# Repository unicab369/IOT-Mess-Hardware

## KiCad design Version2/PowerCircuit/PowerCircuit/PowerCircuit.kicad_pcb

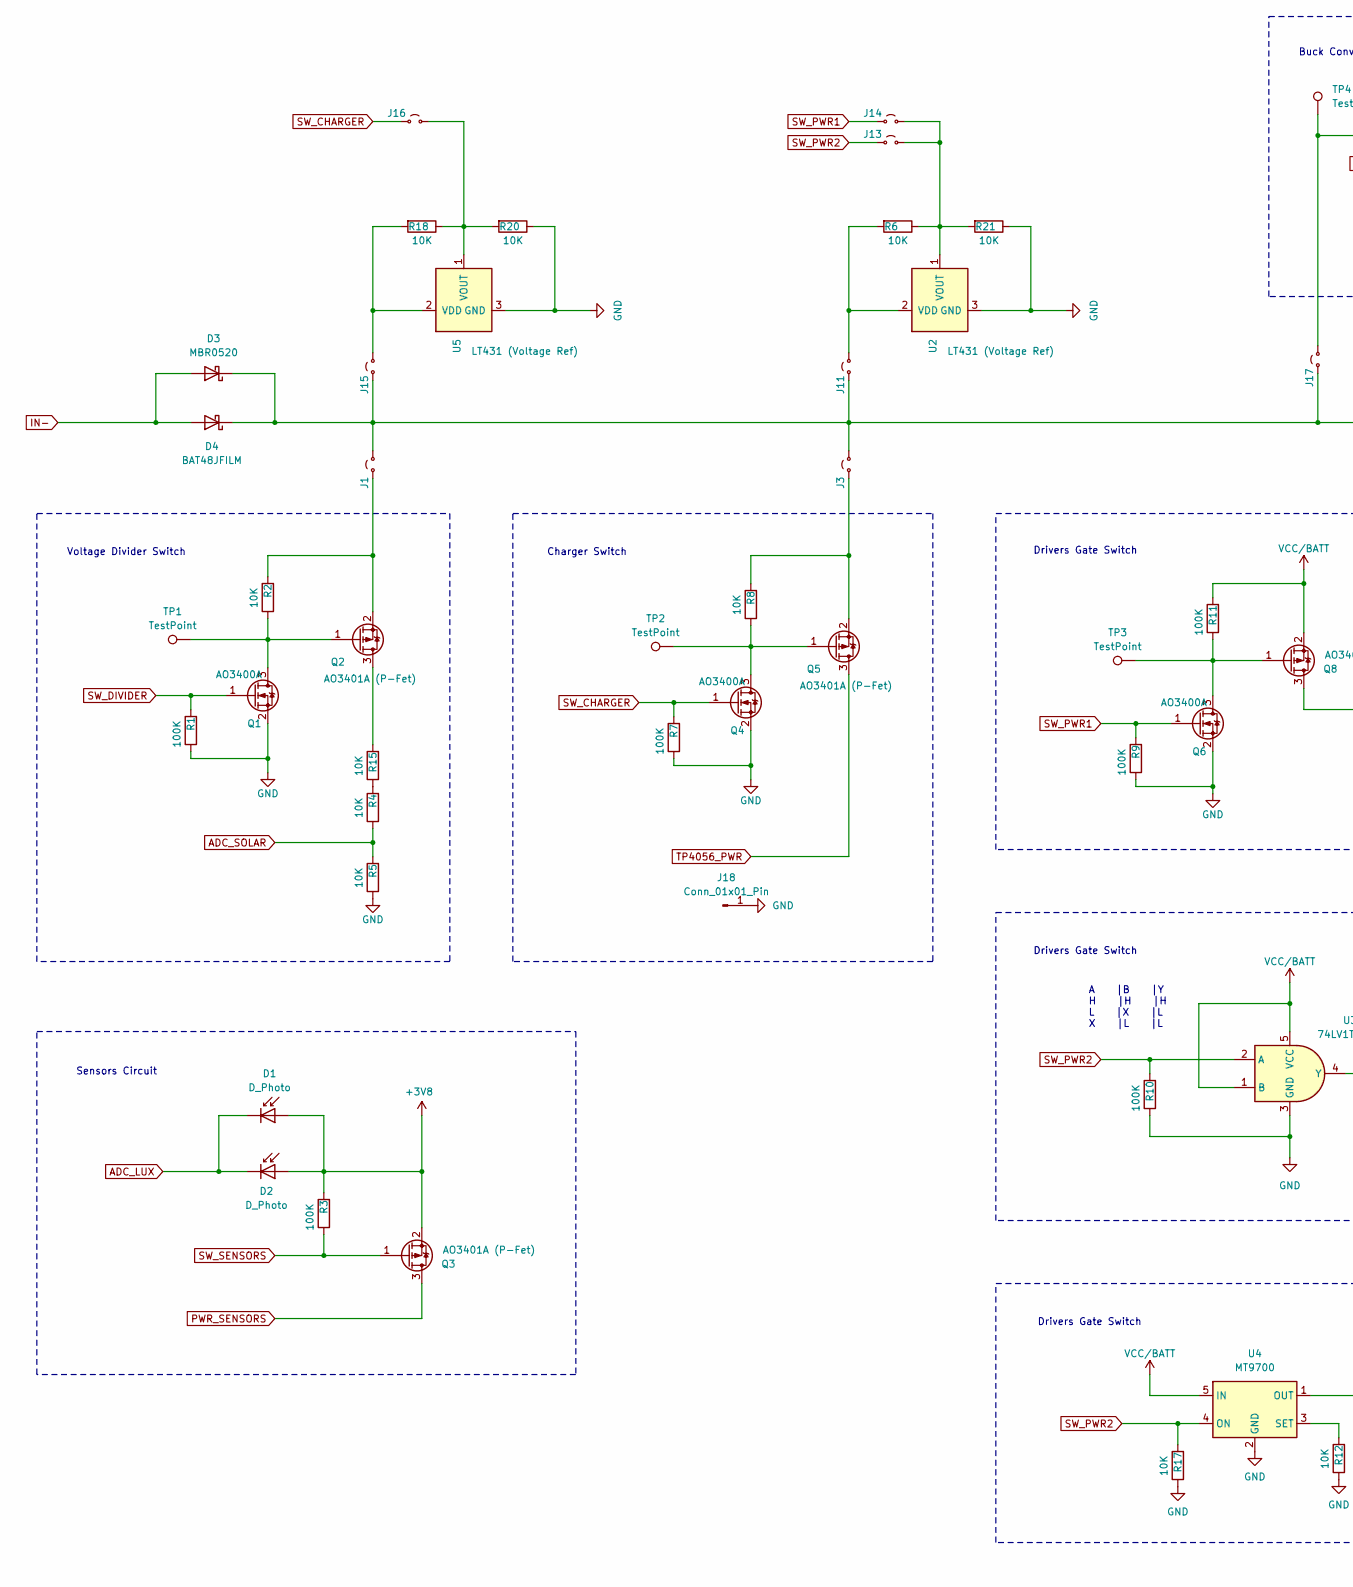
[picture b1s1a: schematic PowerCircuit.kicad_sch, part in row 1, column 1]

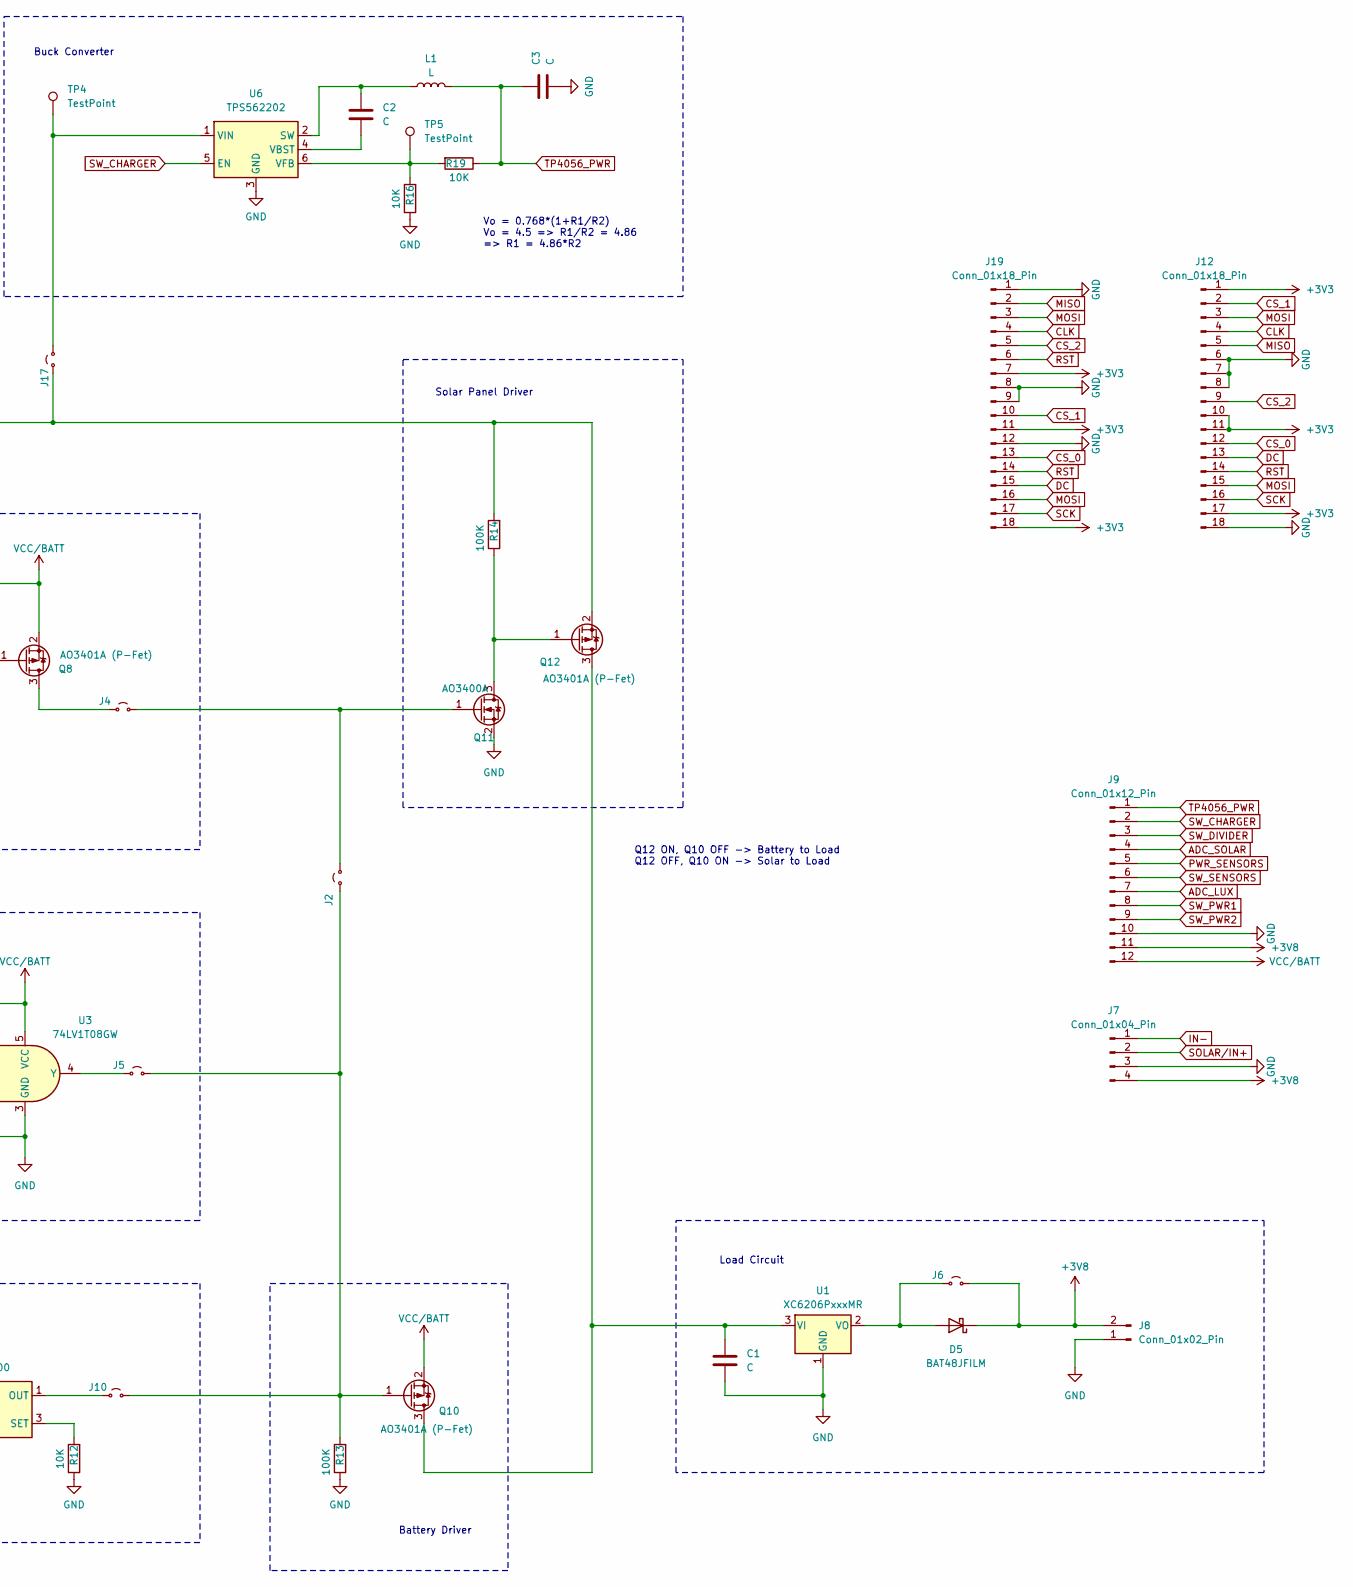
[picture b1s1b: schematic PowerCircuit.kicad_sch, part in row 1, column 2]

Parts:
C1, C2, C3: C; C_0603_1608Metric
D1: D_Photo; LED_0603_1608Metric
D2: D_Photo; LED_0805_2012Metric
D3: MBR0520; D_SOD-123
D4, D5: BAT48JFILM; D_SOD-323
J1, J2, J3, J4, J5, J6, J10, J11, J13, J14, J15, J16, J17: Jumper_2; Jumpper-triangle
J7: Conn_01x04_Pin; PinHeader_1x04_P2.54mm_Vertical
J8: Conn_01x02_Pin; PinHeader_1x02_P1.00mm_Vertical
J9: Conn_01x12_Pin; PinHeader_1x12_P2.54mm_Vertical
J12, J19: Conn_01x18_Pin; PinHeader_1x18_P2.54mm_Vertical
J18: Conn_01x01_Pin; PinHeader_1x01_P2.54mm_Vertical
L1: L; L_Neosid_SMS-ME3010
Q1, Q4, Q6, Q11: AO3400A; SOT-23
Q2, Q3, Q5, Q8, Q10, Q12: AO3401A (P-Fet); SOT-23
R1, R3, R7, R9, R10, R11, R13, R14: 100K; R_0805_2012Metric
R2, R4, R5, R6, R8, R12, R15, R16, R17, R18, R19, R20, R21: 10K; R_0805_2012Metric
TP1, TP2, TP3, TP4, TP5: TestPoint; PinHeader_1x01_P1.00mm_Vertical
U1: XC6206PxxxMR; SOT-23-3
U2, U5: LT431 (Voltage Ref); SOT-23
U3: 74LV1T08GW; SOT-353_SC-70-5
U4: MT9700; SOT-23-5
U6: TPS562202; SOT-563

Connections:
+3V3: J12.1, J12.10, J12.11, J12.17, J19.7, J19.11, J19.18
+3V8: D1.2 (A), D2.2 (A), D5.1 (K), J6.2 (B), J7.4, J8.2, J9.11, Q3.2 (S), R3.2
ADC_LUX: D1.1 (K), D2.1 (K), J9.7
ADC_SOLAR: J9.4, R4.1, R5.2
CLK: J12.4, J19.4
CS_0: J12.12, J19.13
CS_1: J12.2, J19.10
CS_2: J12.9, J19.5
DC: J12.13, J19.15
GND: C1.2, C3.1, J7.3, J8.1, J9.10, J12.6, J12.7, J12.8, J12.18, J18.1, J19.1, J19.8, J19.9, J19.12, Q1.2 (S), Q4.2 (S), Q6.2 (S), Q11.2 (S), R1.1, R5.1, R7.1, R9.1, R10.1, R12.1, R13.1, R16.1, R17.1, R20.1, R21.1, U1.1 (GND), U2.3 (GND), U3.3 (GND), U4.2 (GND), U5.3 (GND), U6.3 (GND)
IN-: D3.2 (A), D4.2 (A), J7.1
MISO: J12.5, J19.2
MOSI: J12.3, J12.15, J19.3, J19.16
unnamed: D3.1 (K), D4.1 (K), J1.2 (B), J3.2 (B), J11.1 (A), J15.1 (A), J17.1 (A), Q12.2 (S), R14.2
unnamed: D5.2 (A), J6.1 (A), U1.2 (VO)
unnamed: J1.1 (A), Q2.2 (S), R2.2
unnamed: J2.2 (B), J4.2 (B), Q11.1 (G)
unnamed: J3.1 (A), Q5.2 (S), R8.2
unnamed: J4.1 (A), Q8.3 (D)
unnamed: J5.1 (A), U3.4 (Y)
unnamed: J10.1 (A), U4.1 (OUT)
unnamed: J2.1 (A), J5.2 (B), J10.2 (B), Q10.1 (G), R13.2
unnamed: J11.2 (B), R6.2, U2.2 (VDD)
unnamed: J13.2 (B), J14.2 (B), R6.1, R21.2, U2.1 (VOUT)
unnamed: J15.2 (B), R18.2, U5.2 (VDD)
unnamed: J16.2 (B), R18.1, R20.2, U5.1 (VOUT)
unnamed: J17.2 (B), TP4.1, U6.1 (VIN)
unnamed: Q1.3 (D), Q2.1 (G), R2.1, TP1.1
unnamed: Q2.3 (D), R15.2
unnamed: Q4.3 (D), Q5.1 (G), R8.1, TP2.1
unnamed: Q6.3 (D), Q8.1 (G), R11.1, TP3.1
unnamed: C1.1, Q10.3 (D), Q12.3 (D), U1.3 (VI)
unnamed: Q11.3 (D), Q12.1 (G), R14.1
unnamed: R4.2, R15.1
unnamed: R12.2, U4.3 (SET)
unnamed: C2.2, L1.1, U6.2 (SW)
unnamed: C2.1, U6.4 (VBST)
unnamed: R16.2, R19.2, TP5.1, U6.6 (VFB)
PWR_SENSORS: J9.5, Q3.3 (D)
RST: J12.14, J19.6, J19.14
SCK: J12.16, J19.17
SOLAR/IN+: J7.2
SW_CHARGER: J9.2, J16.1 (A), Q4.1 (G), R7.2, U6.5 (EN)
SW_DIVIDER: J9.3, Q1.1 (G), R1.2
SW_PWR1: J9.8, J14.1 (A), Q6.1 (G), R9.2
SW_PWR2: J9.9, J13.1 (A), R10.2, R17.2, U3.2 (A), U4.4 (ON)
SW_SENSORS: J9.6, Q3.1 (G), R3.1
TP4056_PWR: C3.2, J9.1, L1.2, Q5.3 (D), R19.1
VCC/BATT: J9.12, Q8.2 (S), Q10.2 (S), R11.2, U3.1 (B), U3.5 (VCC), U4.5 (IN)

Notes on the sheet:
Drivers Gate Switch
Solar Panel Driver
A |B |Y H |H |H L |X |L X |L |L
Voltage Divider Switch
Buck Converter
Load Circuit
Sensors Circuit
Q12 ON, Q10 OFF -> Battery to Load Q12 OFF, Q10 ON -> Solar to Load
Charger Switch
Battery Driver
Vo = 0.768*(1+R1/R2) Vo = 4.5 => R1/R2 = 4.86 => R1 = 4.86*R2

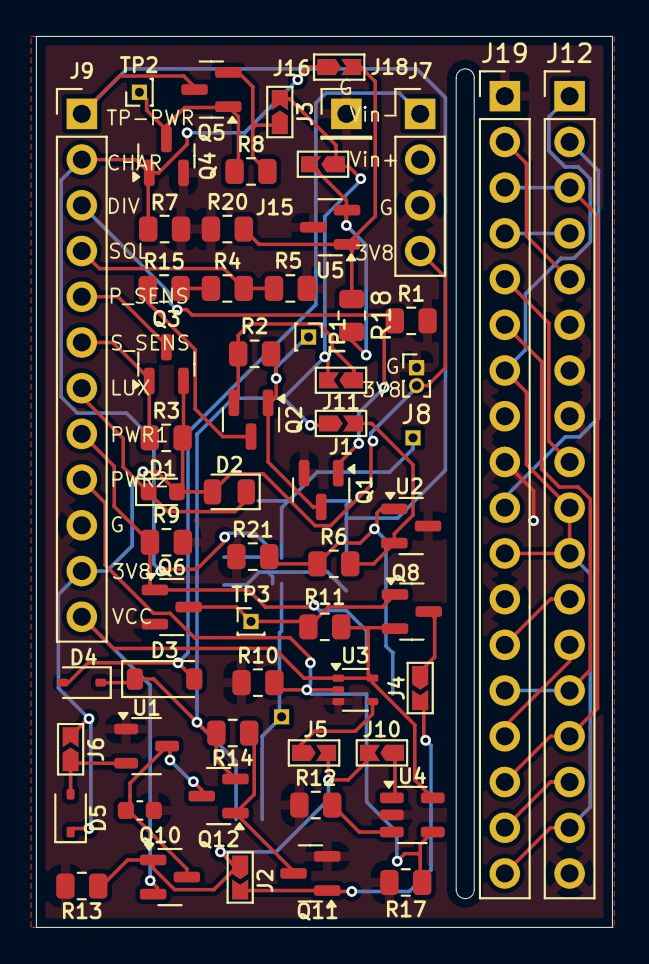
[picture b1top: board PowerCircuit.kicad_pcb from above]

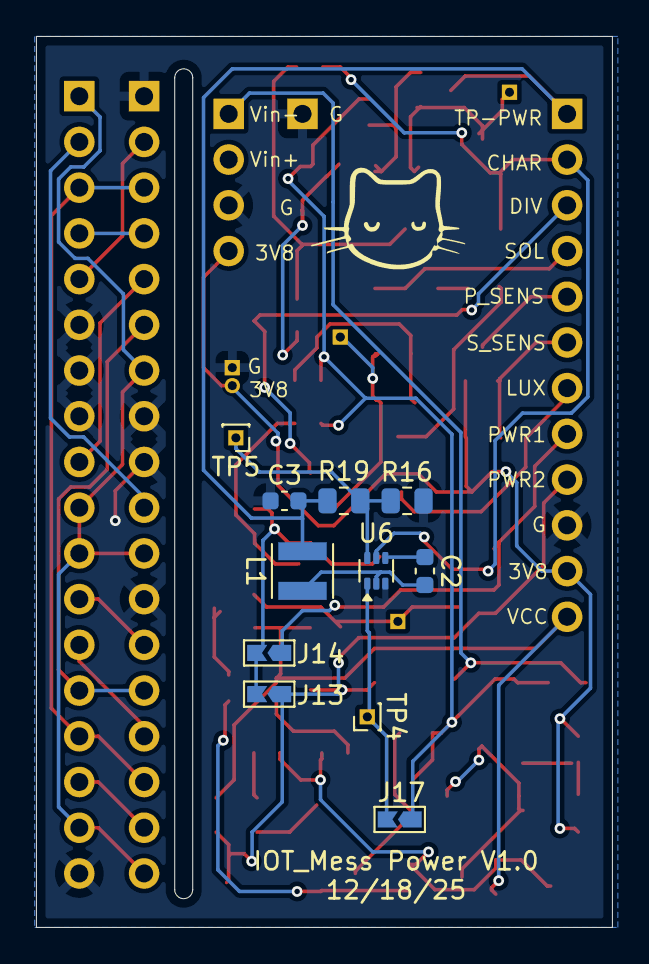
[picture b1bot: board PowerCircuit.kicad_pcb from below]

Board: 2 copper layers, 32.0 x 49.5 mm, 70 parts (11 on the bottom side), 48 nets.

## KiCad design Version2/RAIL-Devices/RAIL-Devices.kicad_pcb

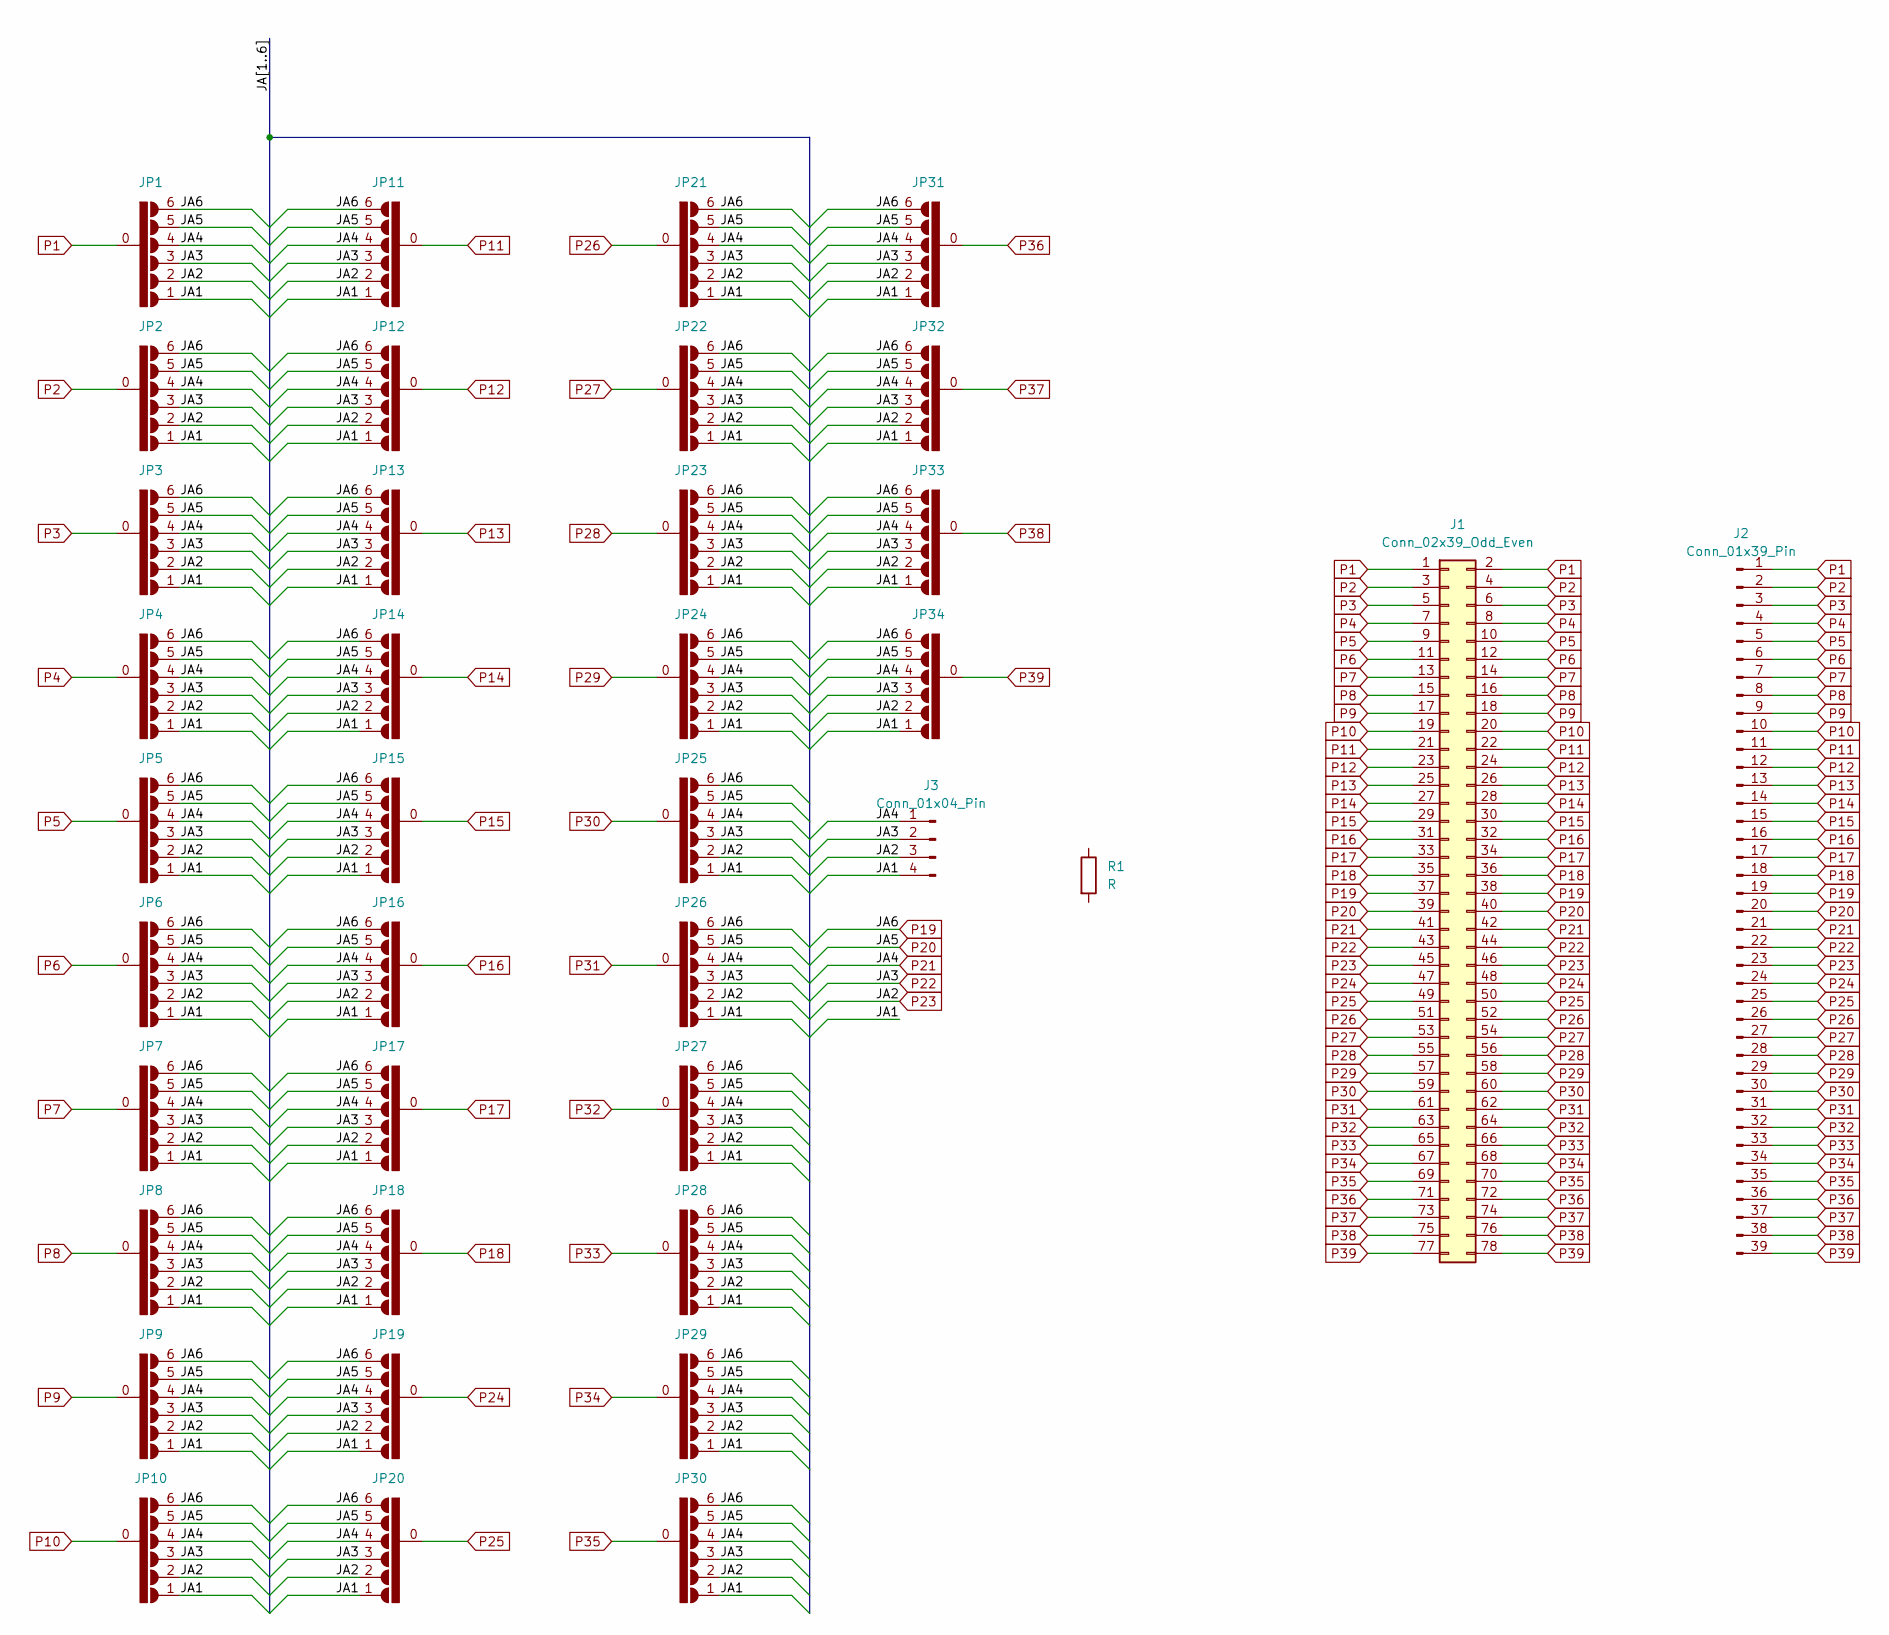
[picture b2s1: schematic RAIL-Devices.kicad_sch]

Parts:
J1: Conn_02x39_Odd_Even; PinHeader_2x39_P2.54mm_Vertical
J2: Conn_01x39_Pin; PinHeader_1x39_P2.54mm_Vertical
J3: Conn_01x04_Pin; PinHeader_1x04_P2.54mm_Vertical
JP1, JP2, JP3, JP4, JP5, JP6, JP7, JP8, JP9, JP10, JP11, JP12, JP13, JP14, JP15, JP16, JP17, JP18, JP19, JP20, JP21, JP22, JP23, JP24, JP25, JP26, JP27, JP28, JP29, JP30, JP31, JP32, JP33, JP34: Jumper6x1
R1: R; R_0603_1608Metric_Pad0.98x0.95mm_HandSolder

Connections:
/JA1: J3.4, JP1.1 (B), JP2.1 (B), JP3.1 (B), JP4.1 (B), JP5.1 (B), JP6.1 (B), JP7.1 (B), JP8.1 (B), JP9.1 (B), JP10.1 (B), JP11.1 (B), JP12.1 (B), JP13.1 (B), JP14.1 (B), JP15.1 (B), JP16.1 (B), JP17.1 (B), JP18.1 (B), JP19.1 (B), JP20.1 (B), JP21.1 (B), JP22.1 (B), JP23.1 (B), JP24.1 (B), JP25.1 (B), JP26.1 (B), JP27.1 (B), JP28.1 (B), JP29.1 (B), JP30.1 (B), JP31.1 (B), JP32.1 (B), JP33.1 (B), JP34.1 (B)
P1: J1.1, J1.2, J2.1, JP1.0 (C)
P2: J1.3, J1.4, J2.2, JP2.0 (C)
P3: J1.5, J1.6, J2.3, JP3.0 (C)
P4: J1.7, J1.8, J2.4, JP4.0 (C)
P5: J1.9, J1.10, J2.5, JP5.0 (C)
P6: J1.11, J1.12, J2.6, JP6.0 (C)
P7: J1.13, J1.14, J2.7, JP7.0 (C)
P8: J1.15, J1.16, J2.8, JP8.0 (C)
P9: J1.17, J1.18, J2.9, JP9.0 (C)
P10: J1.19, J1.20, J2.10, JP10.0 (C)
P11: J1.21, J1.22, J2.11, JP11.0 (C)
P12: J1.23, J1.24, J2.12, JP12.0 (C)
P13: J1.25, J1.26, J2.13, JP13.0 (C)
P14: J1.27, J1.28, J2.14, JP14.0 (C)
P15: J1.29, J1.30, J2.15, JP15.0 (C)
P16: J1.31, J1.32, J2.16, JP16.0 (C)
P17: J1.33, J1.34, J2.17, JP17.0 (C)
P18: J1.35, J1.36, J2.18, JP18.0 (C)
P19: J1.37, J1.38, J2.19, JP1.6 (B), JP2.6 (B), JP3.6 (B), JP4.6 (B), JP5.6 (B), JP6.6 (B), JP7.6 (B), JP8.6 (B), JP9.6 (B), JP10.6 (B), JP11.6 (B), JP12.6 (B), JP13.6 (B), JP14.6 (B), JP15.6 (B), JP16.6 (B), JP17.6 (B), JP18.6 (B), JP19.6 (B), JP20.6 (B), JP21.6 (B), JP22.6 (B), JP23.6 (B), JP24.6 (B), JP25.6 (B), JP26.6 (B), JP27.6 (B), JP28.6 (B), JP29.6 (B), JP30.6 (B), JP31.6 (B), JP32.6 (B), JP33.6 (B), JP34.6 (B)
P20: J1.39, J1.40, J2.20, JP1.5, JP2.5, JP3.5, JP4.5, JP5.5, JP6.5, JP7.5, JP8.5, JP9.5, JP10.5, JP11.5, JP12.5, JP13.5, JP14.5, JP15.5, JP16.5, JP17.5, JP18.5, JP19.5, JP20.5, JP21.5, JP22.5, JP23.5, JP24.5, JP25.5, JP26.5, JP27.5, JP28.5, JP29.5, JP30.5, JP31.5, JP32.5, JP33.5, JP34.5
P21: J1.41, J1.42, J2.21, J3.1, JP1.4 (B), JP2.4 (B), JP3.4 (B), JP4.4 (B), JP5.4 (B), JP6.4 (B), JP7.4 (B), JP8.4 (B), JP9.4 (B), JP10.4 (B), JP11.4 (B), JP12.4 (B), JP13.4 (B), JP14.4 (B), JP15.4 (B), JP16.4 (B), JP17.4 (B), JP18.4 (B), JP19.4 (B), JP20.4 (B), JP21.4 (B), JP22.4 (B), JP23.4 (B), JP24.4 (B), JP25.4 (B), JP26.4 (B), JP27.4 (B), JP28.4 (B), JP29.4 (B), JP30.4 (B), JP31.4 (B), JP32.4 (B), JP33.4 (B), JP34.4 (B)
P22: J1.43, J1.44, J2.22, J3.2, JP1.3 (B), JP2.3 (B), JP3.3 (B), JP4.3 (B), JP5.3 (B), JP6.3 (B), JP7.3 (B), JP8.3 (B), JP9.3 (B), JP10.3 (B), JP11.3 (B), JP12.3 (B), JP13.3 (B), JP14.3 (B), JP15.3 (B), JP16.3 (B), JP17.3 (B), JP18.3 (B), JP19.3 (B), JP20.3 (B), JP21.3 (B), JP22.3 (B), JP23.3 (B), JP24.3 (B), JP25.3 (B), JP26.3 (B), JP27.3 (B), JP28.3 (B), JP29.3 (B), JP30.3 (B), JP31.3 (B), JP32.3 (B), JP33.3 (B), JP34.3 (B)
P23: J1.45, J1.46, J2.23, J3.3, JP1.2 (B), JP2.2 (B), JP3.2 (B), JP4.2 (B), JP5.2 (B), JP6.2 (B), JP7.2 (B), JP8.2 (B), JP9.2 (B), JP10.2 (B), JP11.2 (B), JP12.2 (B), JP13.2 (B), JP14.2 (B), JP15.2 (B), JP16.2 (B), JP17.2 (B), JP18.2 (B), JP19.2 (B), JP20.2 (B), JP21.2 (B), JP22.2 (B), JP23.2 (B), JP24.2 (B), JP25.2 (B), JP26.2 (B), JP27.2 (B), JP28.2 (B), JP29.2 (B), JP30.2 (B), JP31.2 (B), JP32.2 (B), JP33.2 (B), JP34.2 (B)
P24: J1.47, J1.48, J2.24, JP19.0 (C)
P25: J1.49, J1.50, J2.25, JP20.0 (C)
P26: J1.51, J1.52, J2.26, JP21.0 (C)
P27: J1.53, J1.54, J2.27, JP22.0 (C)
P28: J1.55, J1.56, J2.28, JP23.0 (C)
P29: J1.57, J1.58, J2.29, JP24.0 (C)
P30: J1.59, J1.60, J2.30, JP25.0 (C)
P31: J1.61, J1.62, J2.31, JP26.0 (C)
P32: J1.63, J1.64, J2.32, JP27.0 (C)
P33: J1.65, J1.66, J2.33, JP28.0 (C)
P34: J1.67, J1.68, J2.34, JP29.0 (C)
P35: J1.69, J1.70, J2.35, JP30.0 (C)
P36: J1.71, J1.72, J2.36, JP31.0 (C)
P37: J1.73, J1.74, J2.37, JP32.0 (C)
P38: J1.75, J1.76, J2.38, JP33.0 (C)
P39: J1.77, J1.78, J2.39, JP34.0 (C)

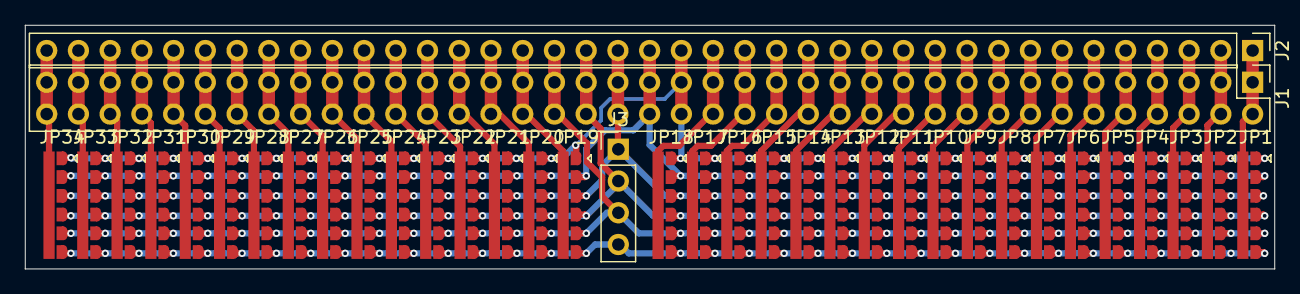
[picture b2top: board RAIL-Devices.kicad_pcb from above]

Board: 2 copper layers, 100.0 x 19.5 mm, 37 parts (0 on the bottom side), 40 nets.
